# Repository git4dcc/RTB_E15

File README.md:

# RTB_E15

This E15 module implements a 12 channel WS2811 emulator with compatible bus timing to drive multiplex (charlieplexing) LEDs. The E15 may be cascaded with regular WS28xx chips. The number of LEDs attached is automatically detected (0-12). The LED voltage is fixed to 5V.  The intended use is to drive Multiplex Signals on Model Railway layouts via the WS28xx bus.

_Note: The E15 is nearly identical to the [RTB_E13](/../../../../git4dcc/RTB_E13), but only allows fixed LED voltage._

<details>
<summary>See also</summary>

- [RTB_E10](/../../../../git4dcc/RTB_E10)
- [RTB_E13](/../../../../git4dcc/RTB_E13)

</details>

<details>
<summary>User Guides</summary>

- [User Guide - DE](https://rtb4dcc.de/ws2811_guide_de/)
- User Guide - EN

</details>

The decoder has the following features,
- **Protocol**
  - WS2811 compatible timing
- **LED ports**
  - 0..12 LEDs (auto detecting)
  - Charlieplexing (Multiplexing) output
  - 256 step PWM (300Hz)
  - LED voltage fixed to 5V (see also [RTB_E13](https://github.com/git4dcc/RTB_E13))
  - gamma correction (optional)
- firmware update via V24 debug interface

# Hardware
My current PCB layout uses SMD footprints with 0.5mm pitch and 0603 parts. Reflow soldering is my recommendation, but with some experience handsoldering is also possible.

## PCB
- 2-layer PCB, FR4, 1.6mm
- CPU: AVR64DA32
- BUS: WS28xx
- LED: Charlieplexing

## Kicad
[Schematic](doc/E15_schematic.pdf) | [Layout](doc/E15_layout.pdf) | [BOM](doc/E15_BOM.pdf) | [Gerber](gerber)

<details>
<summary>Dependency</summary>
<br>

:yellow_circle: Requires my Kicad project library [RTB_SamacSys](/../../../../git4dcc/RTB_SamacSys) in the same directory tree.

</details>

## Firmware
Filename structure: { **pcb** }{ **code** }{ **version** }.hex

Example: **E15F0001**.hex

|   | Description |
| --- | --- |
| **pcb** | Name of matching hardware (**E15**) |
| **code** | Type of code contained (**R**=rom, **B**=bootloader, **F**=flash, **U**=bld update, **P**=UPDI factory code) |
| **version** | Release version (**####**) |

## UPDI
The fuse settings as well as the P-code (E15Pxxxx.hex) has to be installed by using UPDI.<br>

<details>
<summary>Details</summary>

| Fuse Setting | P-code Install |
| --- | --- |
|||

</details>

## Debug Interface
Subsequent code updates can be done via the built-in serial debug interface.<br>

<details>
<summary>Details</summary>

- connect the serial cable **(1Mb, 8N1, RTS/CTS)**
- press 'break' within the VT100 terminal to bump the module to console prompt
- upload the firmware file (E15Fxxxx.hex)
- for more details, refer to the 'User Guide'

</details>

# Software
The LED intensity values for the individual LEDs need to be transmitted over the bus, with N being the number of configured LEDs.

```
Byte order:     {led_0} ... {led_N}
```

# Images

This project is intended for hobby use only and is distributed in accordance with the Apache License 2.0 agreement.

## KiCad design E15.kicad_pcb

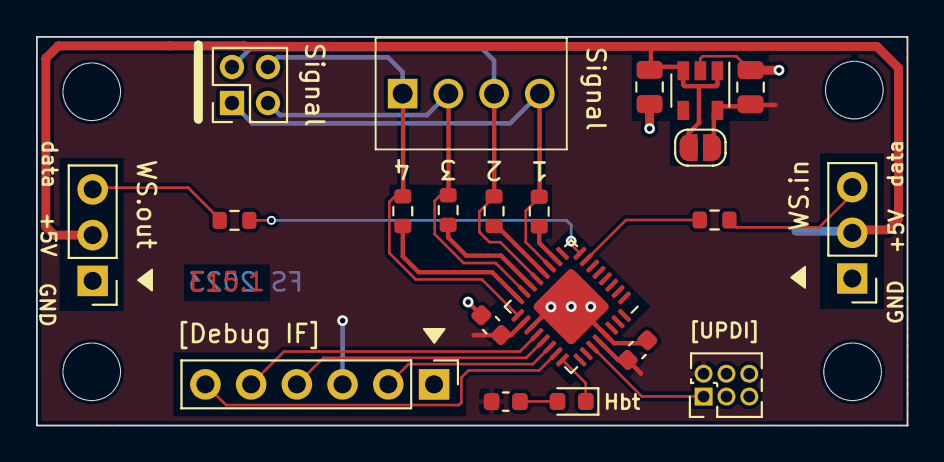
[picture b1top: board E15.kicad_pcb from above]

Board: 2 copper layers, 48.4 x 21.6 mm, 26 parts (1 on the bottom side), 22 nets.

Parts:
C1, C4: 4.7u/10V; C_0805_2012Metric
C2, C3: 100n; C_0603_1608Metric
D1: SSA33L; D_SMA
D2: HBT(green); LED_0603_1608Metric
H1, H2, H3, H4: MountingHole; MountingHole_3.2mm_M3_DIN965
J1: MPX output; PinHeader_2x02_P2.00mm_Vertical
J2: WS-bus output; PinHeader_1x03_P2.54mm_Vertical
J3: WS-bus input; PinHeader_1x03_P2.54mm_Vertical
J4: UPDI IF; PinHeader_2x03_P1.27mm_Vertical
J5: Debug IF; PinHeader_1x06_P2.54mm_Vertical
J7: MPX output; 1725672
JP1: SolderJumper_2_Open; SolderJumper-2_P1.3mm_Open_RoundedPad1.0x1.5mm
R14, R15, R16, R17: 120; R_0603_1608Metric
R18, R19: 160; R_0603_1608Metric
R20: 3.3k; R_0603_1608Metric
U1: AVR-64da32; QFN-32-1EP_5x5mm_P0.5mm_EP3.1x3.1mm
U2: MIC5205-5.0YM5; SOT-23-5

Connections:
+5V: C1.1, D1.1, J2.2, J3.2, JP1.1, U2.1, U2.3
DI: J3.3, R18.2
DO: J2.3, R19.2
GND: C1.2, C2.2, C3.2, C4.2, D1.2, J2.1, J3.1, J4.6, J5.1, U1.19, U1.29, U1.33, U2.2
unnamed: D2.1, U1.24
unnamed: D2.2, R20.1
unnamed: R14.1, U1.16
unnamed: R15.1, U1.14
unnamed: R16.1, U1.12
unnamed: R17.1, U1.10
unnamed: R18.1, U1.7
unnamed: R19.1, U1.8
OUT1: J1.1, J7.4, R17.2, U1.11
OUT2: J1.2, J7.3, R16.2, U1.13
OUT3: J1.3, J7.2, R15.2, U1.15
OUT4: J1.4, J7.1, R14.2, U1.17
UPDI: J4.1, U1.27
V24.cts: J5.6, U1.23
V24.rts: J5.2, U1.22
V24.rx: J5.4, U1.21
V24.tx: J5.5, U1.20
VDD: C2.1, C3.1, C4.1, J4.2, J5.3, JP1.2, R20.2, U1.18, U1.28, U2.5

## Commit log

2024-04-15 initial
2024-10-04 Added local images
2024-11-14 mod: documentation
2025-03-17 add: MPX device finger print file
2025-03-19 add: preconfig files E15Exxxx ...
2025-03-22 add: supplemental
2026-02-20 Update README links to relative paths
2026-02-20 git mirror test

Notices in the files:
E15.kicad_pcb:
Licensed under the Apache License, Version 2
